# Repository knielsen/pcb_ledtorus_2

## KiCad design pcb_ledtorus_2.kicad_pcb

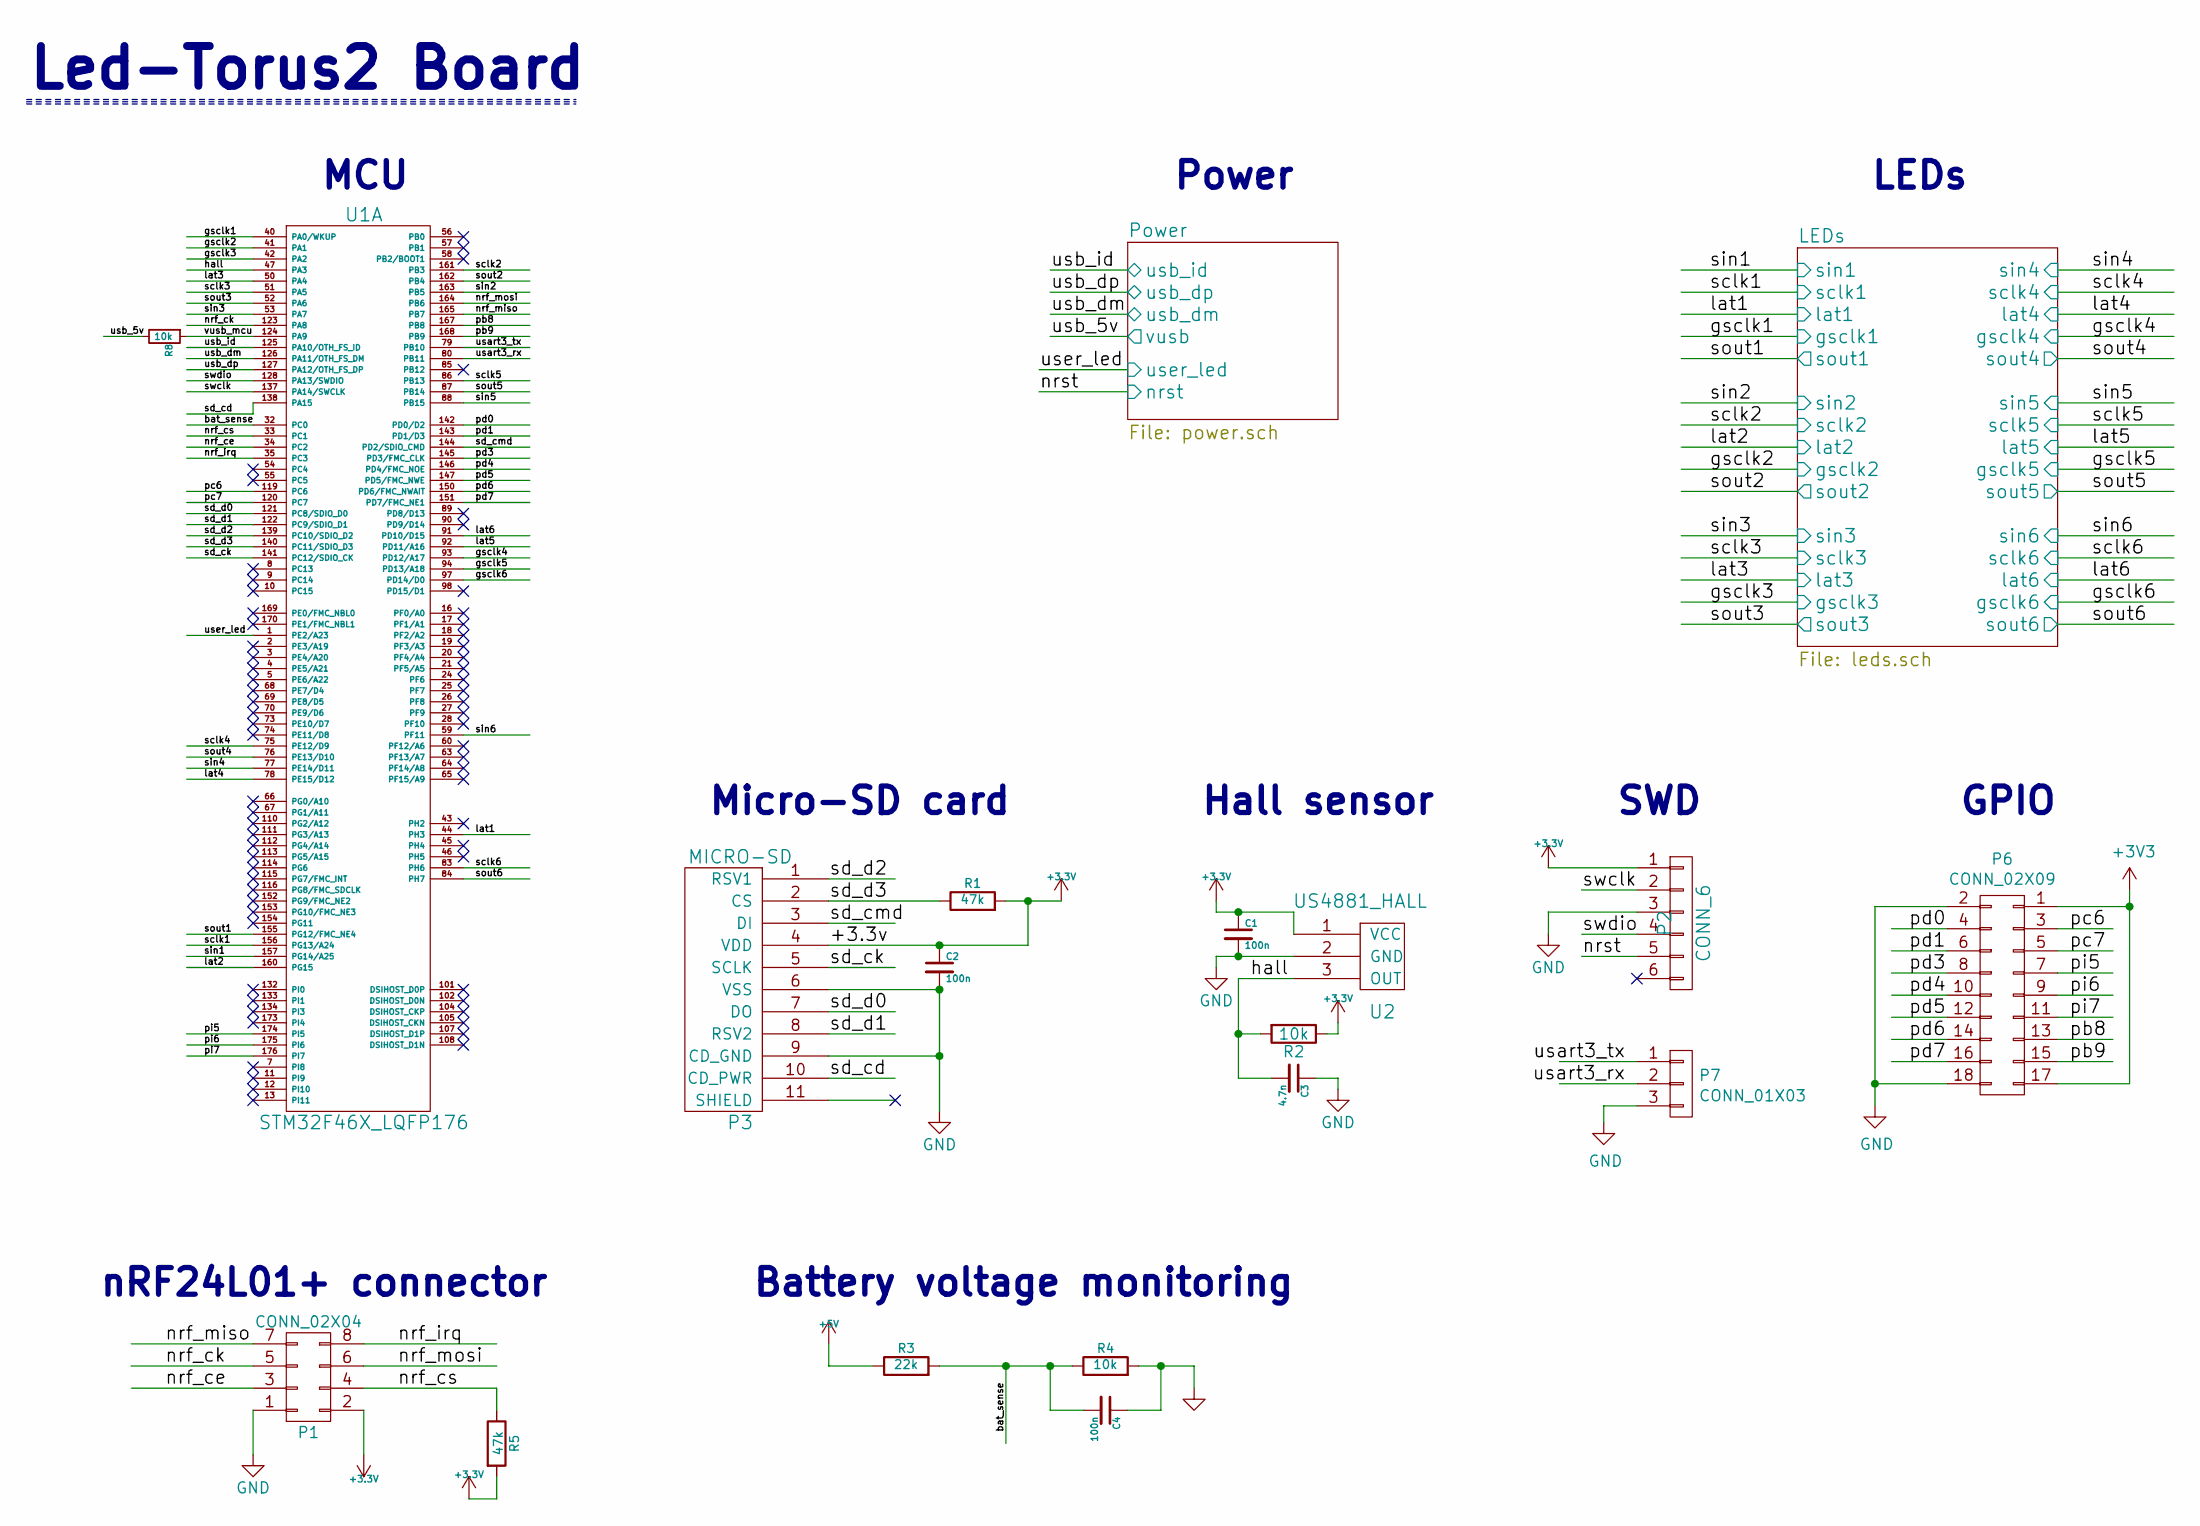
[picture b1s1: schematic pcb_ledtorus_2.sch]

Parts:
C1, C2, C4: 100n; c_0603
C3: 4.7n; c_0805
P1: CONN_02X04; pin_socket_4x2
P2: CONN_6; pin_strip_6
P3: MICRO-SD; SD_502774
P6: CONN_02X09; Pin_Header_Straight_2x09
P7: CONN_01X03; Pin_Header_Straight_1x03
R1, R5: 47k; r_0805
R2, R4, R8: 10k; r_0805
R3: 22k; r_0805
U1: STM32F46X_LQFP176; LQFP-176
U2: US4881_HALL; TO-92_Inline_Narrow_Oval

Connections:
+5V: R3.1; also elsewhere on the board
/bat_sense: C4.2, R3.2, R4.1, U1.32 (PC0)
/gsclk1: U1.40 (PA0/WKUP); also elsewhere on the board
/gsclk2: U1.41 (PA1); also elsewhere on the board
/gsclk3: U1.42 (PA2); also elsewhere on the board
/gsclk4: U1.93 (PD12/A17); also elsewhere on the board
/gsclk5: U1.94 (PD13/A18); also elsewhere on the board
/gsclk6: U1.97 (PD14/D0); also elsewhere on the board
/hall: C3.2, R2.2, U1.47 (PA3), U2.3 (OUT)
/lat1: U1.44 (PH3); also elsewhere on the board
/lat2: U1.160 (PG15); also elsewhere on the board
/lat3: U1.50 (PA4); also elsewhere on the board
/lat4: U1.78 (PE15/D12); also elsewhere on the board
/lat5: U1.92 (PD11/A16); also elsewhere on the board
/lat6: U1.91 (PD10/D15); also elsewhere on the board
/nrf_ce: P1.3, U1.34 (PC2)
/nrf_ck: P1.5, U1.123 (PA8)
/nrf_cs: P1.4, R5.1, U1.33 (PC1)
/nrf_irq: P1.8, U1.35 (PC3)
/nrf_miso: P1.7, U1.165 (PB7)
/nrf_mosi: P1.6, U1.164 (PB6)
/nrst: P2.5; also elsewhere on the board
/pb8: P6.13, U1.167 (PB8)
/pb9: P6.15, U1.168 (PB9)
/pc6: P6.3, U1.119 (PC6)
/pc7: P6.5, U1.120 (PC7)
/pd0: P6.4, U1.142 (PD0/D2)
/pd1: P6.6, U1.143 (PD1/D3)
/pd3: P6.8, U1.145 (PD3/FMC_CLK)
/pd4: P6.10, U1.146 (PD4/FMC_NOE)
/pd5: P6.12, U1.147 (PD5/FMC_NWE)
/pd6: P6.14, U1.150 (PD6/FMC_NWAIT)
/pd7: P6.16, U1.151 (PD7/FMC_NE1)
/pi5: P6.7, U1.174 (PI5)
/pi6: P6.9, U1.175 (PI6)
/pi7: P6.11, U1.176 (PI7)
/sclk1: U1.156 (PG13/A24); also elsewhere on the board
/sclk2: U1.161 (PB3); also elsewhere on the board
/sclk3: U1.51 (PA5); also elsewhere on the board
/sclk4: U1.75 (PE12/D9); also elsewhere on the board
/sclk5: U1.86 (PB13); also elsewhere on the board
/sclk6: U1.83 (PH6); also elsewhere on the board
/sd_cd: P3.10 (CD_PWR), U1.138 (PA15)
/sd_ck: P3.5 (SCLK), U1.141 (PC12/SDIO_CK)
/sd_cmd: P3.3 (DI), U1.144 (PD2/SDIO_CMD)
/sd_d0: P3.7 (DO), U1.121 (PC8/SDIO_D0)
/sd_d1: P3.8 (RSV2), U1.122 (PC9/SDIO_D1)
/sd_d2: P3.1 (RSV1), U1.139 (PC10/SDIO_D2)
/sd_d3: P3.2 (CS), R1.1, U1.140 (PC11/SDIO_D3)
/sin1: U1.157 (PG14/A25); also elsewhere on the board
/sin2: U1.163 (PB5); also elsewhere on the board
/sin3: U1.53 (PA7); also elsewhere on the board
/sin4: U1.77 (PE14/D11); also elsewhere on the board
/sin5: U1.88 (PB15); also elsewhere on the board
/sin6: U1.59 (PF11); also elsewhere on the board
/sout1: U1.155 (PG12/FMC_NE4); also elsewhere on the board
/sout2: U1.162 (PB4); also elsewhere on the board
/sout3: U1.52 (PA6); also elsewhere on the board
/sout4: U1.76 (PE13/D10); also elsewhere on the board
/sout5: U1.87 (PB14); also elsewhere on the board
/sout6: U1.84 (PH7); also elsewhere on the board
/swclk: P2.2, U1.137 (PA14/SWCLK)
/swdio: P2.4, U1.128 (PA13/SWDIO)
/usart3_rx: P7.2, U1.80 (PB11)
/usart3_tx: P7.1, U1.79 (PB10)
/usb_5v: R8.2; also elsewhere on the board
/usb_dm: U1.126 (PA11/OTH_FS_DM); also elsewhere on the board
/usb_dp: U1.127 (PA12/OTH_FS_DP); also elsewhere on the board
/usb_id: U1.125 (PA10/OTH_FS_ID); also elsewhere on the board
/user_led: U1.1 (PE2/A23); also elsewhere on the board
/vusb_mcu: R8.1, U1.124 (PA9)
GND: C1.2, C2.2, C3.1, C4.1, P1.1, P2.3, P3.6 (VSS), P3.9 (CD_GND), P6.2, P6.18, P7.3, R4.2, U2.2 (GND); also elsewhere on the board

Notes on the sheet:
MCU
Led-Torus2 Board
nRF24L01+ connector
Micro-SD card
Battery voltage monitoring
SWD
Hall sensor
GPIO
Power
LEDs

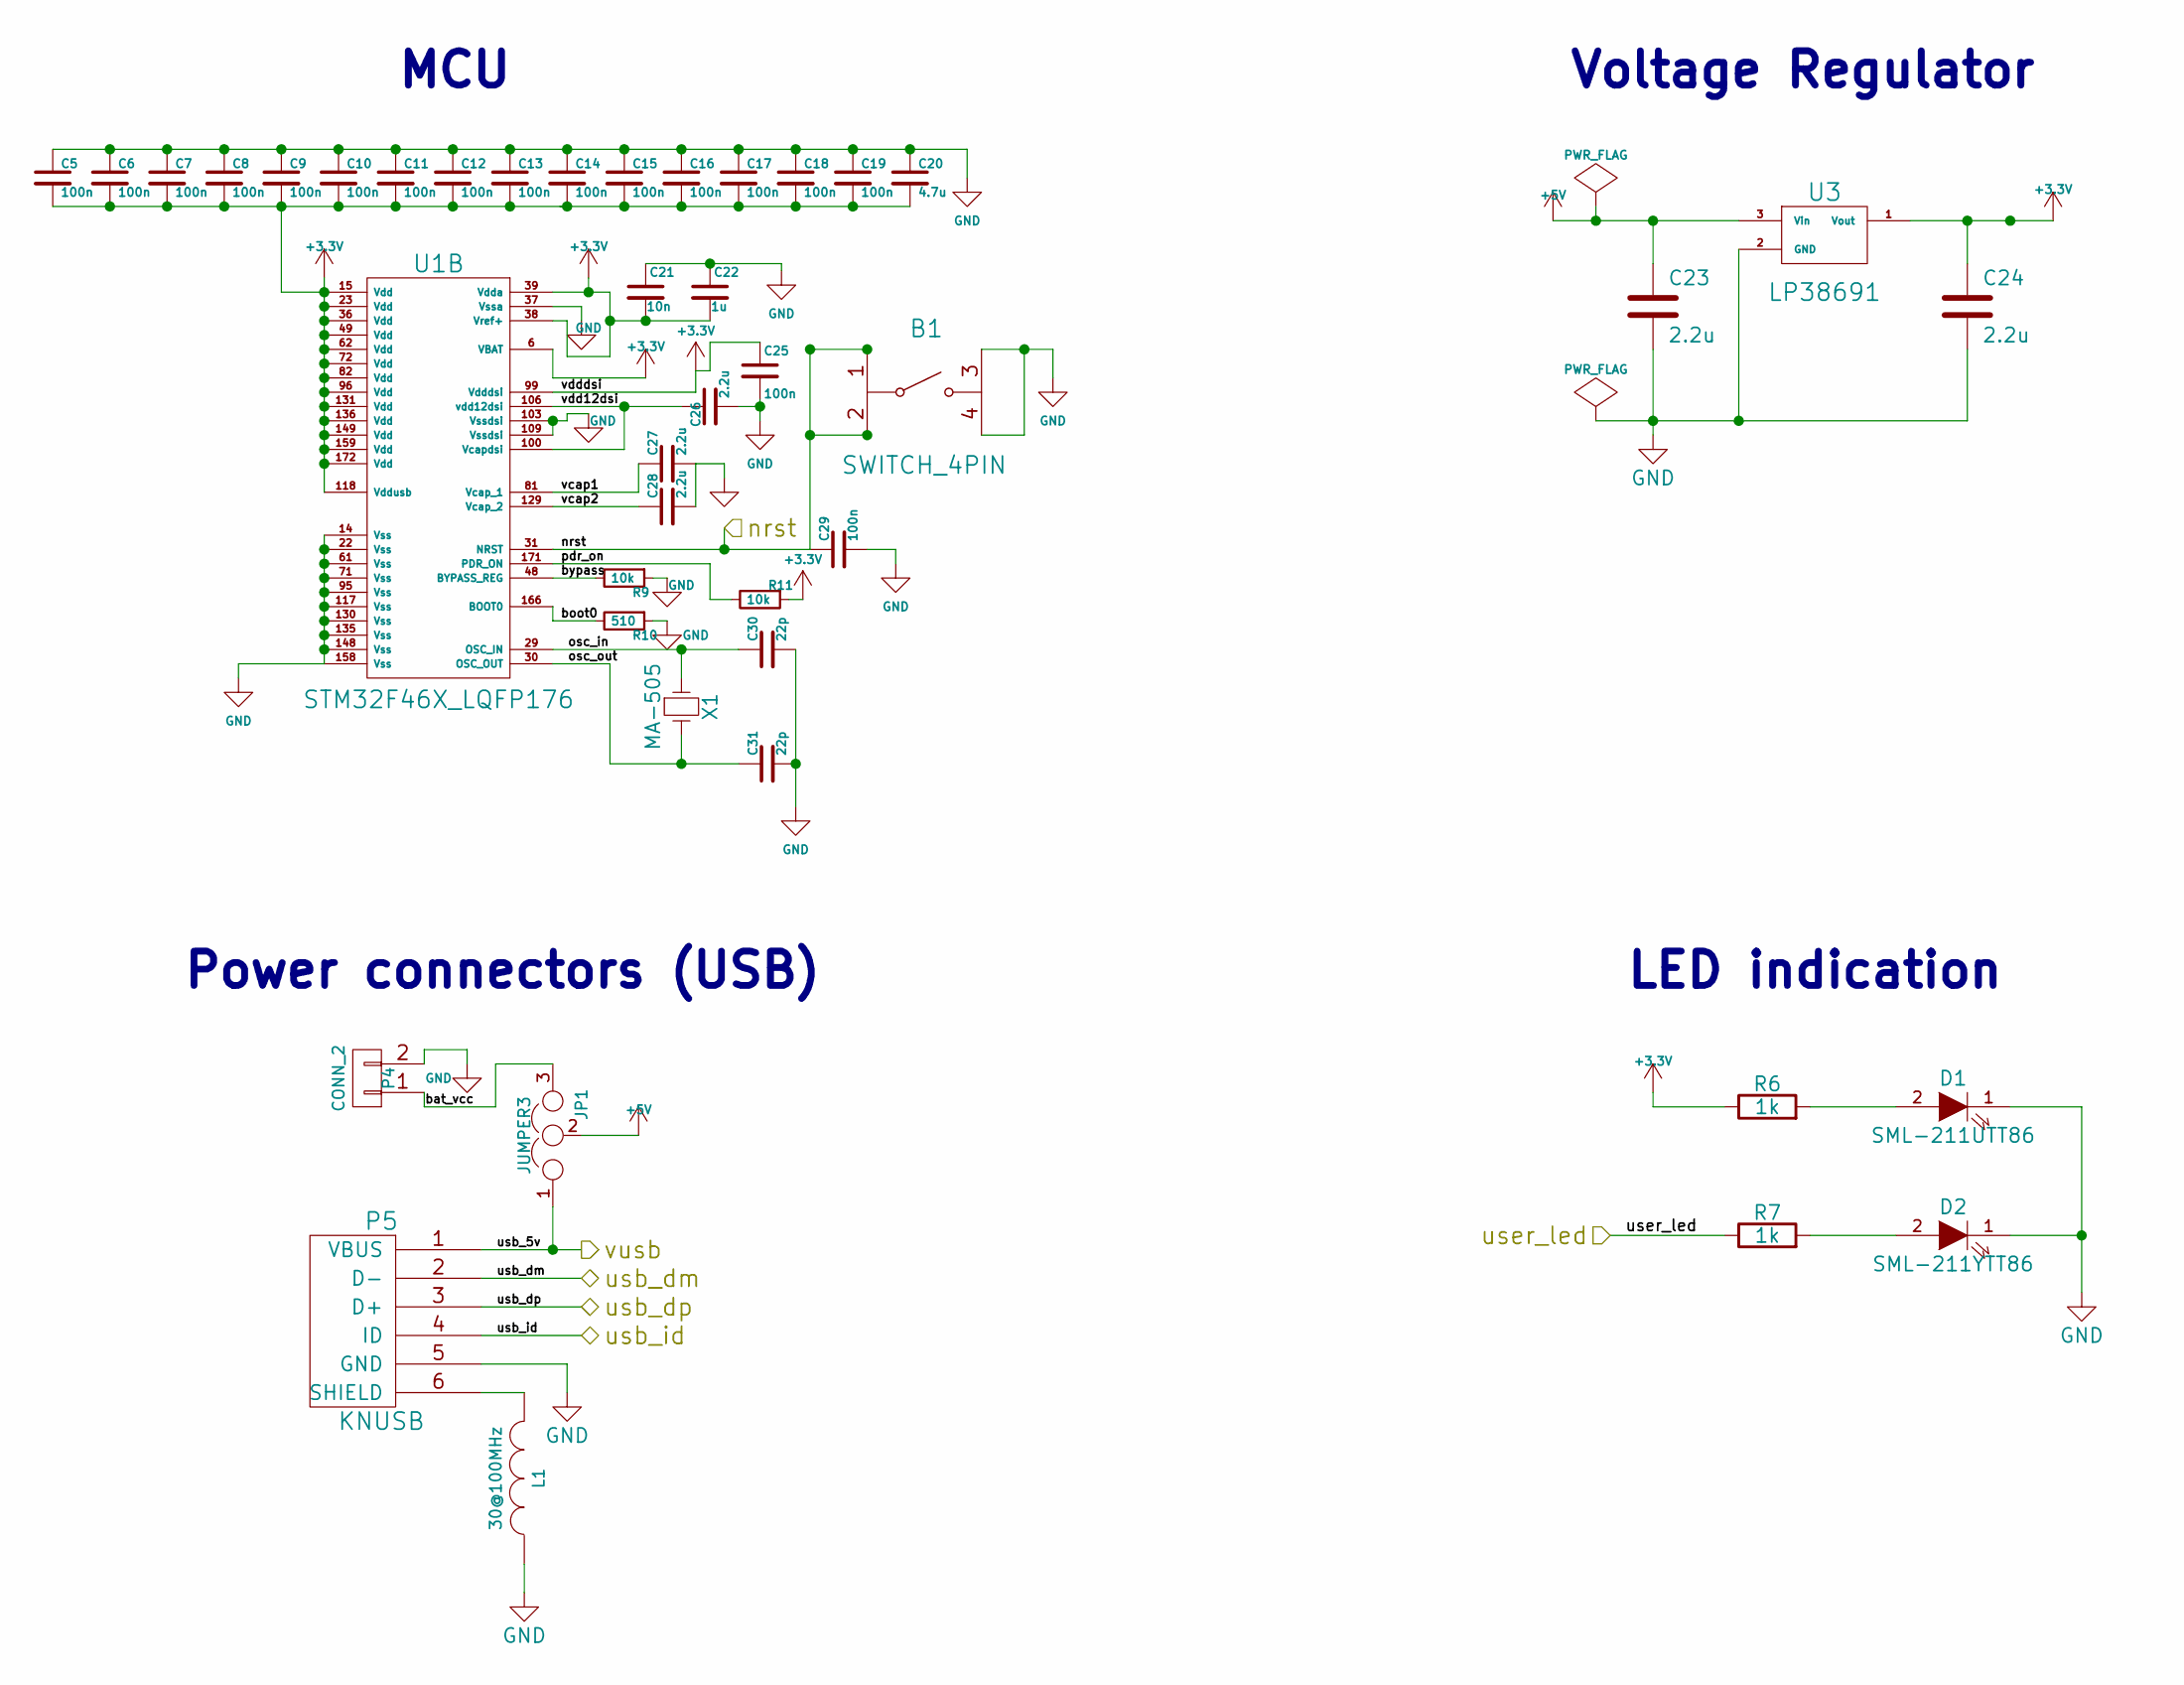
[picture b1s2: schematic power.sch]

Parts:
B1: SWITCH_4PIN; SWITCH_FSMJSMA
C5, C6, C7, C8, C9, C10, C11, C12, C13, C14, C15, C16, C17, C18, C19, C25, C29: 100n; c_0603
C20: 4.7u; c_0805
C21: 10n; c_0805
C22: 1u; c_0805
C23, C24, C26, C27, C28: 2.2u; c_0805
C30, C31: 22p; c_0805
D1: SML-211UTT86; LED_0805
D2: SML-211YTT86; LED_0805
JP1: JUMPER3; pin_strip_3
L1: 30@100MHz; c_0603
P4: CONN_2; pin_strip_2-90
P5: KNUSB; 10103594-0001LF
R6, R7: 1k; r_0805
R9, R11: 10k; r_0805
R10: 510; r_0805
U1: STM32F46X_LQFP176; LQFP-176
U3: LP38691; TO-252-3
X1: MA-505; 2-SOJ

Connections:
+5V: C23.1, JP1.2, U3.3 (Vin); also elsewhere on the board
/Power/bat_vcc: JP1.3, P4.1
/Power/boot0: R10.2, U1.166 (BOOT0)
/Power/bypass: R9.2, U1.48 (BYPASS_REG)
/Power/osc_in: C30.1, U1.29 (OSC_IN), X1.1
/Power/osc_out: C31.1, U1.30 (OSC_OUT), X1.2
/Power/pdr_on: R11.2, U1.171 (PDR_ON)
/Power/vcap1: C27.1, U1.81 (Vcap_1)
/Power/vcap2: C28.1, U1.129 (Vcap_2)
/Power/vdd12dsi: C26.1, U1.100 (Vcapdsi), U1.106 (vdd12dsi)
/nrst: B1.1, B1.2, C29.1, U1.31 (NRST); also elsewhere on the board
/usb_5v: JP1.1, P5.1 (VBUS); also elsewhere on the board
/usb_dm: P5.2 (D-); also elsewhere on the board
/usb_dp: P5.3 (D+); also elsewhere on the board
/usb_id: P5.4 (ID); also elsewhere on the board
/user_led: R7.1; also elsewhere on the board
GND: B1.3, B1.4, C5.1, C6.1, C7.1, C8.1, C9.1, C10.1, C11.1, C12.1, C13.1, C14.1, C15.1, C16.1, C17.1, C18.1, C19.1, C20.1, C21.1, C22.1, C23.2, C24.2, C25.2, C26.2, C27.2, C28.2, C29.2, C30.2, C31.2, D1.1 (K), D2.1 (K), L1.1, P4.2, P5.5 (GND), R9.1, R10.1, U1.14 (Vss), U1.22 (Vss), U1.37 (Vssa), U1.61 (Vss), U1.71 (Vss), U1.95 (Vss), U1.103 (Vssdsi), U1.109 (Vssdsi), U1.117 (Vss), U1.130 (Vss), U1.135 (Vss), U1.148 (Vss), U1.158 (Vss), U3.2 (GND); also elsewhere on the board
unnamed: D1.2 (A), R6.2
unnamed: D2.2 (A), R7.2
unnamed: L1.2, P5.6 (SHIELD)

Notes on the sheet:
MCU
Voltage Regulator
Power connectors (USB)
LED indication
